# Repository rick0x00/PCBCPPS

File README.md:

# PCBCPPS
pcb coupled protection for power supply

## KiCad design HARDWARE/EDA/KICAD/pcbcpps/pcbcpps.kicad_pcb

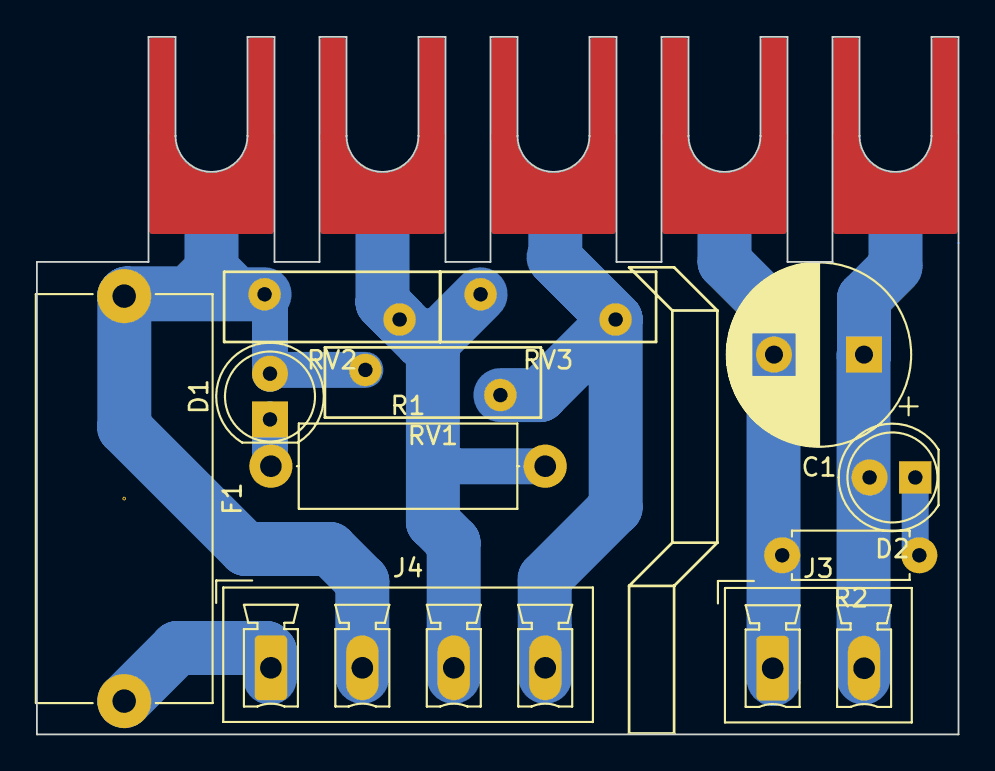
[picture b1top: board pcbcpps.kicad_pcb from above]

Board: 2 copper layers, 51.2 x 38.8 mm, 11 parts (0 on the bottom side), 8 nets.

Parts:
C1: CP; CP_Radial_D10.0mm_P5.00mm
D1, D2: LED; LED_D5.0mm
F1: Fuse; Fuseholder_Cylinder-5x20mm_Schurter_0031_8201_Horizontal_Op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
J3: PWR; PhoenixContact_MCV_1,5_2-G-5.08_1x02_P5.08mm_Vertical
J4: PWR; PhoenixContact_MCV_1,5_4-G-5.08_1x04_P5.08mm_Vertical
R1: 30K 2W; R_Axial_DIN0414_L11.9mm_D4.5mm_P15.24mm_Horizontal
R2: 1K; R_Axial_DIN0207_L6.3mm_D2.5mm_P7.62mm_Horizontal
RV1, RV2, RV3: 275V; RV_Disc_D12mm_W3.9mm_P7.5mm

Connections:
/LINE_OUT: D1.2, F1.1, J4.2, RV1.1, RV2.1
GND: C1.2, J3.1, R2.2
unnamed: C1.1, D2.2, J3.2
unnamed: D1.1, R1.1
unnamed: D2.1, R2.1
unnamed: F1.2, J4.1
unnamed: J4.3, R1.2, RV2.2, RV3.1
unnamed: J4.4, RV1.2, RV3.2

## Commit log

2022-04-16 start project
2022-04-19 complete ajusts
2022-04-20 add image
2022-04-25 adjust conections
2022-04-26 adjust pcb
